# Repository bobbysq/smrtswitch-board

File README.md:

# SMRTSWITCH

An Arduino Nano-based prototyping controller for FRC. Code is available [here](https://github.com/frc4646/smrtswitch).

Render of the board:

Pictures of the final board:

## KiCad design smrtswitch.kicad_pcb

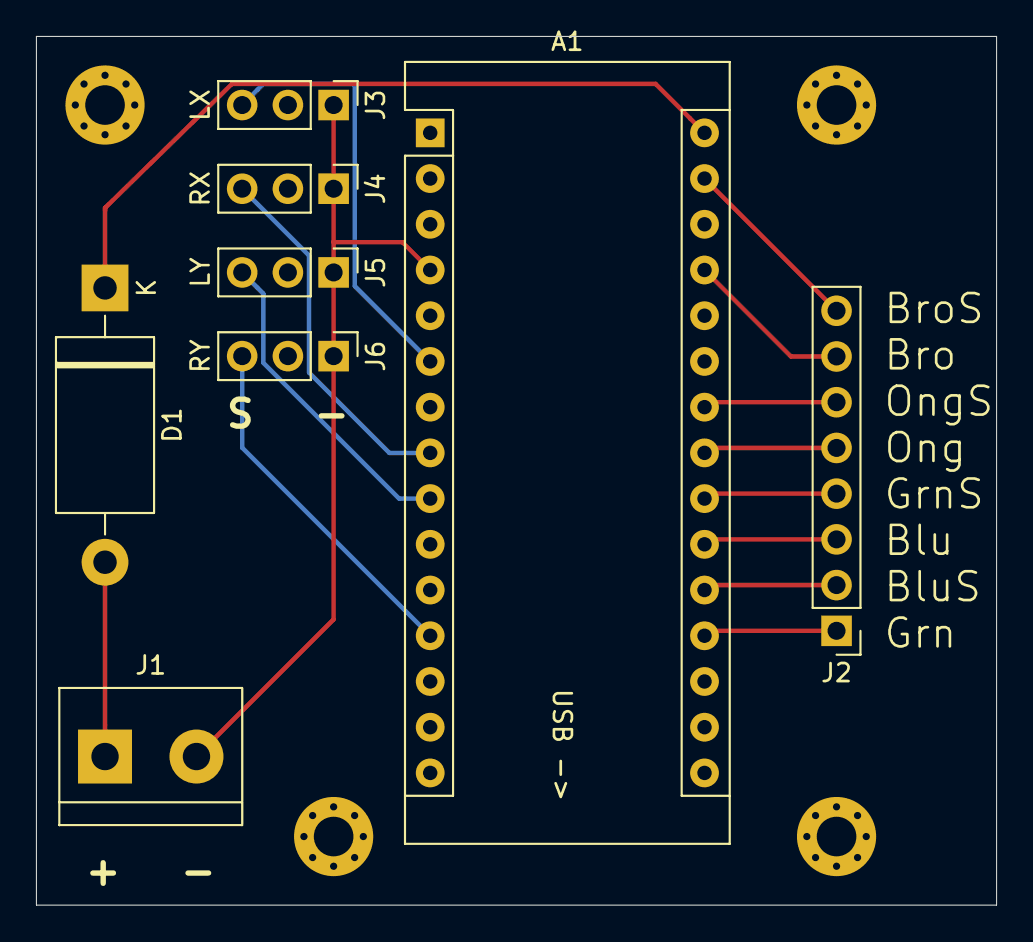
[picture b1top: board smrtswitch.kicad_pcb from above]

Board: 2 copper layers, 53.3 x 48.3 mm, 12 parts (0 on the bottom side), 15 nets.

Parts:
 : Hole; MountingHole_2.2mm_M2_Pad_Via
 #2,  #3,  #4: Hole; MountingHole_2.2mm_M2_Pad_Via
A1: Arduino_Nano_v2.x; Arduino_Nano
D1: 1N53xxB; D_DO-201_P15.24mm_Horizontal
J1: Screw_Terminal; TerminalBlock_bornier-2_P5.08mm
J2: Conn_01x08; PinHeader_1x08_P2.54mm_Vertical
J3: LX; PinHeader_1x03_P2.54mm_Vertical
J4: RX; PinHeader_1x03_P2.54mm_Vertical
J5: LY; PinHeader_1x03_P2.54mm_Vertical
J6: RY; PinHeader_1x03_P2.54mm_Vertical

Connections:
+12V: D1.2, J1.1
GND: A1.4, J1.2, J3.1, J4.1, J5.1, J6.1
unnamed: A1.6, J3.3
unnamed: A1.8, J4.3
unnamed: A1.9, J5.3
unnamed: A1.12, J6.3
unnamed: A1.19, J2.1
unnamed: A1.20, J2.2
unnamed: A1.21, J2.3
unnamed: A1.22, J2.4
unnamed: A1.23, J2.5
unnamed: A1.24, J2.6
unnamed: A1.27, J2.7
unnamed: A1.29, J2.8
unnamed: A1.30, D1.1

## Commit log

2020-06-21 Added README
2024-03-23 long-uncommitted changes
2024-03-23 Added pictures of manufactured board
2024-03-23 Fixed render image link
2024-03-23 nvm it's still up
